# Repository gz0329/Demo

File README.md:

# Demo
Demotrates both programming and circuitry design projects.

circuit_pcb_design contains a collection of test circuits and PCBs that I designed with KiCAD.

script_work contains several script projects that have a variety of functions.
Detailed descriptions are in the code. Python oriented. 

EBI_moisture_sensor is a RF based moisture sensor that can detect water content in wood.
Firmware wise is C oriented. Circuits and PCBs are designed with KiCAD.
It also has several documentation samples such as BoM and Assembly instruction for board manufacturer.

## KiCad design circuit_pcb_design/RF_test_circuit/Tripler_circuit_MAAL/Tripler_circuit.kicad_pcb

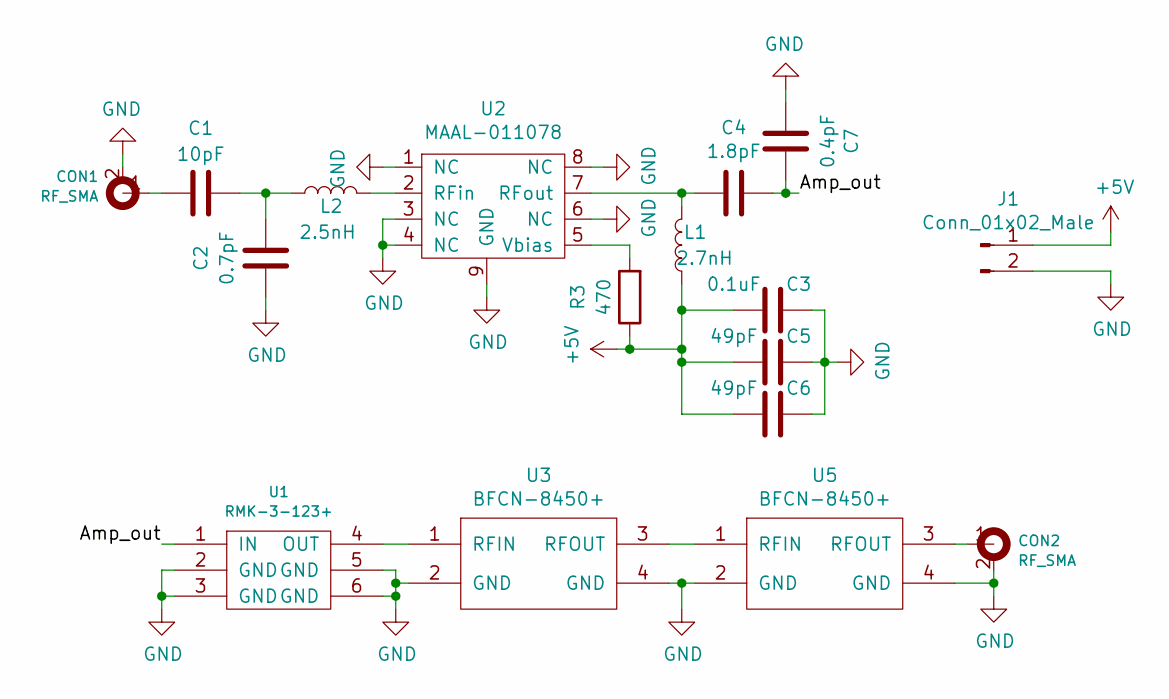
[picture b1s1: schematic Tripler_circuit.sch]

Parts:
C1: 10pF; C_0402
C2: 0.7pF; C_0402
C3: 0.1uF; C_0402
C4: 1.8pF; C_0402
C5, C6: 49pF; C_0603
C7: 0.4pF; C_0201_0603Metric
CON1, CON2: RF_SMA; SMAConnector
J1: Conn_01x02_Male; PinHeader_1x02_P2.54mm_Vertical
L1: 2.7nH; L_0402
L2: 2.5nH; L_0201_0603Metric
R3: 470; R_0603
U1: RMK-3-123+
U2: MAAL-011078
U3, U5: BFCN-8450+

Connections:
+5V: C3.2, C5.2, C6.2, J1.1, L1.1, R3.1
/Amp_out: C4.1, C7.1, U1.1 (IN)
GND: C2.1, C3.1, C5.1, C6.1, C7.2, CON1.2, CON2.2, J1.2, U1.2 (GND), U1.3 (GND), U1.5 (GND), U1.6 (GND), U2.1 (NC), U2.3 (NC), U2.4 (NC), U2.6 (NC), U2.8 (NC), U2.9 (GND), U3.2 (GND), U3.4 (GND), U5.2 (GND), U5.4 (GND)
unnamed: C1.1, CON1.1
unnamed: C1.2, C2.2, L2.1
unnamed: C4.2, L1.2, U2.7 (RFout)
unnamed: CON2.1, U5.3 (RFOUT)
unnamed: L2.2, U2.2 (RFin)
unnamed: R3.2, U2.5 (Vbias)
unnamed: U1.4 (OUT), U3.1 (RFIN)
unnamed: U3.3 (RFOUT), U5.1 (RFIN)

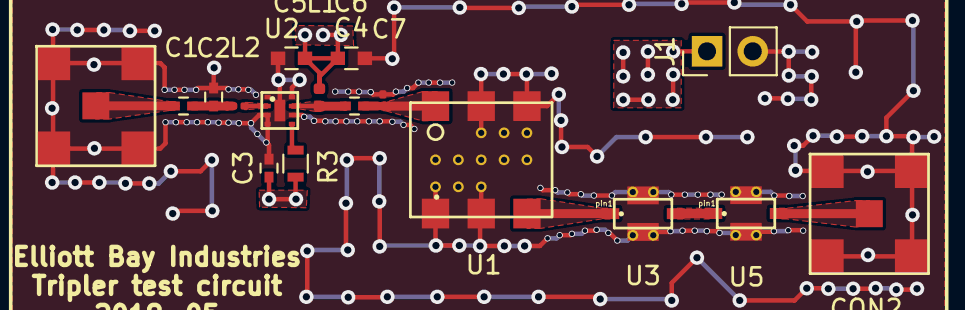
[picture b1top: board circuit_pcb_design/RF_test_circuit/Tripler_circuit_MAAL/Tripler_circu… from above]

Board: 4 copper layers, 17 parts (0 on the bottom side), 11 nets.

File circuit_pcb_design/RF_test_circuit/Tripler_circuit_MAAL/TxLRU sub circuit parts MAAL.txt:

TxLRU sub circuit parts MAAL

Amplifier
https://www.digikey.com/product-detail/en/MAAL-011078-TR1000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

2.5nH inductor 0201
https://www.digikey.com/product-detail/en/taiyo-yuden/HKQ060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

2.7nH inductor 0402
https://www.digikey.com/product-detail/en/taiyo-yuden/HK1005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

10pF cap 0402
https://www.digikey.com/product-detail/en/yageo/CC0402JRNPO9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

0.7pF cap 0402
https://www.digikey.com/product-detail/en/yageo/CC0402BRNPO9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

0.4pF cap 0201
https://www.digikey.com/product-detail/en/taiyo-yuden/UMK063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

1.8pF cap 0402
https://www.digikey.com/product-detail/en/yageo/CC0402CRNPO9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

0.1uF cap 0402
https://www.digikey.com/product-detail/en/taiyo-yuden/EMK105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

49pF cap 0603
https://www.digikey.com/product-detail/en/avx-corporation/06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

470ohm res 0603
https://www.digikey.com/product-detail/en/yageo/RC0603FR-074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

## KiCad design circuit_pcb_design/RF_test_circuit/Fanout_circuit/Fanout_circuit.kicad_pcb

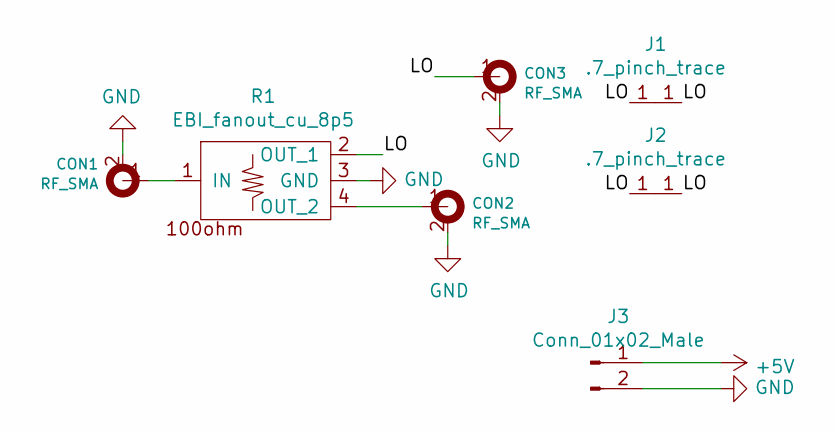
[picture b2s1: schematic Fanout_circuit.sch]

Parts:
CON1, CON2, CON3: RF_SMA; SMAConnector
J1, J2: .7_pinch_trace
J3: Conn_01x02_Male; PinHeader_1x02_P2.54mm_Vertical
R1: EBI_fanout_cu_8p5

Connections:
+5V: J3.1
/LO: CON3.1, J1.1, J2.1, R1.2 (OUT_1)
GND: CON1.2, CON2.2, CON3.2, J3.2, R1.3 (GND)
unnamed: CON1.1, R1.1 (IN)
unnamed: CON2.1, R1.4 (OUT_2)

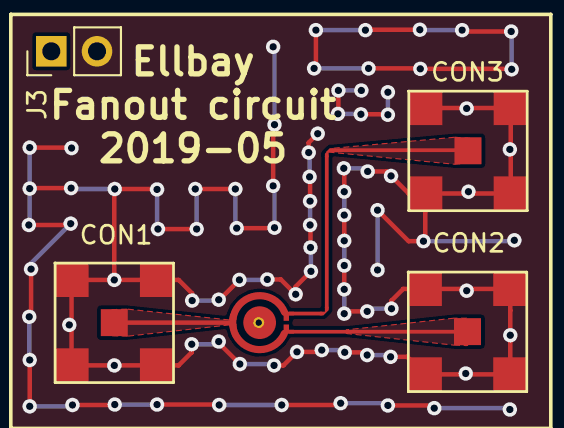
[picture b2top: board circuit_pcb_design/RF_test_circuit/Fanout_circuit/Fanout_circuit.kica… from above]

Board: 4 copper layers, 7 parts (0 on the bottom side), 4 nets.

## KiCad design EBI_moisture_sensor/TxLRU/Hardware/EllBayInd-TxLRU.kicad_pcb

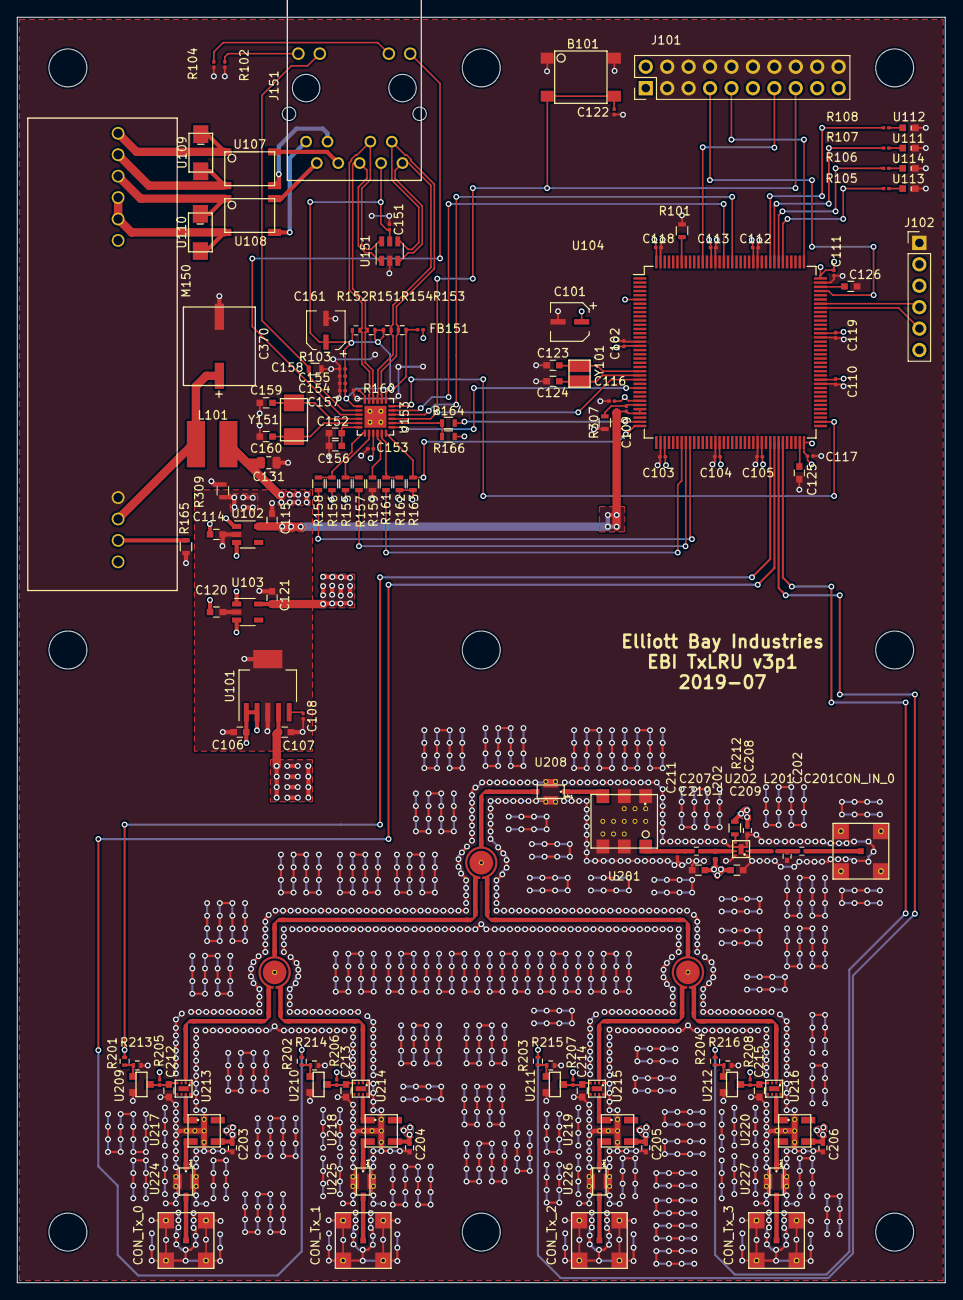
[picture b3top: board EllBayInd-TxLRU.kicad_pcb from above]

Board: 4 copper layers, 110.0 x 150.0 mm, 167 parts (0 on the bottom side), 96 nets.

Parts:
B101: Reset; Tactile_switch
C101, C161: 4.7uF; CP_Elec_4.3x4.3
C102, C103, C104, C105, C109, C110, C111, C112, C113, C116, C117, C118, C119, C122, C151, C153, C154, C155, C157, C158: 100nF; C_0201_0603Metric
C106, C125, C126: 2.2uF; C_0603
C107, C114, C115, C120, C121, C156: 1uF; C_0603
C108: 0.01uF; C_0201_0603Metric
C123, C124: 4.3pF; C_0603
C131: 10uF; C_0805_2012Metric
C152: 470pF; C_0603
C159, C160: 30pF; C_0603
C201: 10pF; C_0402
C202: 0.7pF; C_0402
C203, C204, C205, C206, C208: 0.1uF; C_0402
C207: 1.8pF; C_0402
C209, C210: 49pF; C_0603
C211: 0.4pF; C_0201_0603Metric
C212, C213, C214, C215: 0.01uF; C_0603
C370: 470uF; 470uF Cap
CON_IN_0: RF_SMA; SMAConnector
CON_Tx_0, CON_Tx_1, CON_Tx_2, CON_Tx_3: RF_SMA; SMAConnector
FB151: 600@100; L_0201_0603Metric
J101: SWD debugging; Program_Pin_Header
J102: Conn_01x06_UART1; PinHeader_1x06_P2.54mm_Vertical
J151: RJ45_7499211122A; RJ45
J201, J202, J203, J204, J205, J206, J207, J208, J209, J210, J211, J212, J213: .7_pinch_trace; .7_pinch_.537_trace
L101: 10uH; 10uH_Inductor
L201: 2.5nH; L_0201_0603Metric
L202: 2.7nH; L_0402
M150: AG9205S
MK201, MK202, MK203, MK204, MK205, MK206, MK207, MK208, MK209: Mounting_hole; MountingHole_4.5mm
R101, R103, R155, R156, R159, R162, R166: 10k; R_0603
R102, R104: 270; R_0201_0603Metric
R105, R106, R107, R108: 750; R_0201_0603Metric
R151, R152, R153, R154: 50; R_0402
R157, R158, R161, R164: 33; R_0603
R160: 12k1; R_0201_0603Metric
R163: 1k5; R_0603
R165: 0; R_0603
R201, R202, R203, R204: 100; R_0402
R205, R206, R207, R208: 4k; R_0201_0603Metric
R209, R210, R211: EBI_fanout_cu_8p5; EBI_fanout_cu_8p5_.537trace
R212: 470; R_0603
R213, R214, R215, R216: 10k; R_0402
R307, R309: Close; R_0603
U101: 5V_REG
U102, U103: 3V3_REG; 3V3REG
U104: STM32H743ZITx; MCU
U107, U108: MDB6S
U109, U110: SMAJ58CA
U111, U112, U113, U114: LED
U151: USBLC6-4SC6; TVS-diode
U153: LAN8742A
U201: RMK-3-123+
U202: MAAL-011078
U208, U224, U225, U226, U227: BFCN-8450+
U209, U210, U211, U212: NFET
U213, U214, U215, U216: MAAL-011130
U217, U218, U219, U220: TCBT-14+
Y101: 8 MHz; 8mhz_crystal
Y151: 25MHz; 25mhz_crystal

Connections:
+3.3VA: C109.1, C115.1, U102.5, U104.32, U104.33
+3V3: C101.1, C102.1, C103.1, C104.1, C105.1, C110.1, C111.1, C112.1, C113.1, C116.1, C117.1, C118.1, C119.1, C121.1, C153.2, FB151.2, J101.1, J101.2, R155.2, R156.2, R162.2, R163.2, R166.2, U103.5, U104.6, U104.17, U104.30, U104.39, U104.52, U104.62, U104.72, U104.84, U104.95, U104.108, U104.121, U104.131, U104.144, U153.9
+5V: C107.1, C203.1, C204.1, C205.1, C206.1, C208.2, C209.2, C210.2, L202.1, R205.2, R206.2, R207.2, R208.2, R212.2, U101.4, U217.3, U218.3, U219.3, U220.3
/Common/5.5V: C106.1, C114.1, C120.1, C131.2, L101.1, U101.1, U101.2, U102.1, U102.3, U103.1, U103.3
/Common/CRS_DV: R161.2, U104.43
/Common/LED0: R105.2, U104.114
/Common/LED1: R106.2, U104.115
/Common/LED2: R107.2, U104.116
/Common/LED3: R108.2, U104.117
/Common/MDC: U104.27, U153.13
/Common/MDIO: R163.1, U104.36, U153.12
/Common/NRST: B101.3, B101.4, C122.1, J101.15, U104.25, U153.15
/Common/RX_D0: R157.2, U104.44
/Common/RX_D1: R158.2, U104.45
/Common/SWCLK: J101.9, U104.109
/Common/SWDIO: J101.7, U104.105
/Common/Sheet5C53D1CF/LED_G: J151.13, R103.1, U153.2
/Common/Sheet5C53D1CF/LED_Y: J151.11, U153.3
/Common/Sheet5C53D1CF/RX+: J151.4, R152.2, U151.6, U153.23
/Common/Sheet5C53D1CF/RX-: J151.5, R151.2, U151.1, U153.22
/Common/Sheet5C53D1CF/TX+: J151.1, R154.2, U151.3, U153.21
/Common/Sheet5C53D1CF/TX-: J151.2, R153.2, U151.4, U153.20
/Common/Sheet5C53D1CF/VC1+: J151.7, U107.4
/Common/Sheet5C53D1CF/VC1-: J151.8, U107.3
/Common/Sheet5C53D1CF/VC2+: J151.9, U108.4
/Common/Sheet5C53D1CF/VC2-: J151.10, U108.3
/Common/TRACESWO: J101.13, U104.133
/Common/TX_D0: U104.128, U153.17
/Common/TX_D1: U104.74, U153.18
/Common/TX_EN: U104.126, U153.16
/Common/UART1_RX: J102.4, U104.102
/Common/UART1_TX: J102.5, U104.101
/Common/nINT: R164.2, U104.35
/LNA_out: C207.1, C211.1, U201.1
/LNA_out_0: U217.2, U224.1
/LNA_out_1: U218.2, U225.1
/LNA_out_2: U219.2, U226.1
/LNA_out_3: U220.2, U227.1
/LO: J201.1, J202.1, J203.1, J204.1, J205.1, J206.1, J207.1, J208.1, J209.1, J210.1, J211.1, J212.1, J213.1, R209.1, R209.2, R209.4, R210.1, R210.2, R210.4, R211.1, R211.2, R211.4, U208.3, U213.2, U214.2, U215.2, U216.2
/Switch_0: R201.2, U104.64
/Switch_1: R202.2, U104.65
/Switch_2: R203.2, U104.66
/Switch_3: R204.2, U104.67
/Tripler_out: U201.4, U208.1
GND: B101.1, B101.2, C101.2, C102.2, C103.2, C104.2, C105.2, C110.2, C111.2, C112.2, C113.2, C116.2, C117.2, C118.2, C119.2, C122.2, C123.2, C124.2, C125.2, C126.2, C131.1, C151.1, C152.1, C153.1, C154.1, C155.1, C156.1, C157.1, C158.1, C159.1, C160.1, C161.2, C202.1, C203.2, C204.2, C205.2, C206.2, C208.1, C209.1, C210.1, C211.2, C212.2, C213.2, C214.2, C215.2, C370.2, CON_IN_0.2, CON_Tx_0.2, CON_Tx_1.2, CON_Tx_2.2, CON_Tx_3.2, J101.3, J101.4, J101.5, J101.6, J101.8, J101.10, J101.12, J101.14, J101.16, J101.18, J101.20, J102.1, M150.7, R101.2, R102.2, R103.2, R104.2, R159.2, R160.1, R165.1, R209.3, R210.3, R211.3, R213.2, R214.2, R215.2, R216.2, R307.2, R309.1, U104.16, U104.38, U104.51, U104.61, U104.83, U104.94, U104.107, U104.120, U104.130, U104.143, U111.1, U112.1, U113.1, U114.1, U151.2, U153.25, U201.2, U201.3, U201.5, U201.6, U202.1, U202.3, U202.4, U202.6, U202.8, U202.9, U208.2, U208.4, U209.3, U210.3, U211.3, U212.3, U213.1, U213.8, U214.1, U214.8, U215.1, U215.8, U216.1, U216.8, U217.5, U218.5, U219.5, U220.5, U224.2, U224.4, U225.2, U225.4, U226.2, U226.4, U227.2, U227.4
GNDA: C109.2, R307.1, U104.31
GNDPWR: C106.2, C107.2, C108.2, C114.2, C115.2, C120.2, C121.2, R309.2, U101.3, U101.6, U102.2, U103.2
unnamed: C108.1, U101.5
unnamed: C123.1, U104.23, Y101.1
unnamed: C124.1, U104.24, Y101.2
unnamed: C125.1, U104.71
unnamed: C126.1, U104.106
unnamed: C151.2, C154.2, C155.2, C157.2, C158.2, C161.1, FB151.1, J151.3, R151.1, R152.1, R153.1, R154.1, U151.5, U153.1, U153.19
unnamed: C152.2, C156.2, U153.6
unnamed: C159.2, U153.4, Y151.2
unnamed: C160.2, U153.5, Y151.1
unnamed: C201.1, C202.2, L201.2
unnamed: C201.2, CON_IN_0.1
unnamed: C207.2, L202.2, U202.7
unnamed: C212.1, R205.1, U209.1, U213.4
unnamed: C213.1, R206.1, U210.1, U214.4
unnamed: C214.1, R207.1, U211.1, U215.4
unnamed: C215.1, R208.1, U212.1, U216.4
unnamed: C370.1, L101.2, M150.8
unnamed: CON_Tx_0.1, U224.3
unnamed: CON_Tx_1.1, U225.3
unnamed: CON_Tx_2.1, U226.3
unnamed: CON_Tx_3.1, U227.3
unnamed: J151.12, R104.1
unnamed: J151.14, R102.1
unnamed: L201.1, U202.2
unnamed: M150.1, U107.1, U109.1
unnamed: M150.2, U107.2, U109.2
unnamed: M150.3, U108.1, U110.1
unnamed: M150.4, M150.5, U108.2, U110.2
unnamed: M150.9, R165.2
unnamed: R101.1, U104.138
unnamed: R105.1, U113.2
unnamed: R106.1, U114.2
unnamed: R107.1, U111.2
unnamed: R108.1, U112.2
unnamed: R155.1, R157.1, U153.8
unnamed: R156.1, R158.1, U153.7
unnamed: R159.1, U153.10
unnamed: R160.2, U153.24
unnamed: R161.1, R162.1, U153.11
unnamed: R164.1, R166.1, U153.14
unnamed: R201.1, R213.1, U209.2
unnamed: R202.1, R214.1, U210.2
unnamed: R203.1, R215.1, U211.2
unnamed: R204.1, R216.1, U212.2
unnamed: R212.1, U202.5
unnamed: U213.7, U217.1
unnamed: U214.7, U218.1
unnamed: U215.7, U219.1
unnamed: U216.7, U220.1

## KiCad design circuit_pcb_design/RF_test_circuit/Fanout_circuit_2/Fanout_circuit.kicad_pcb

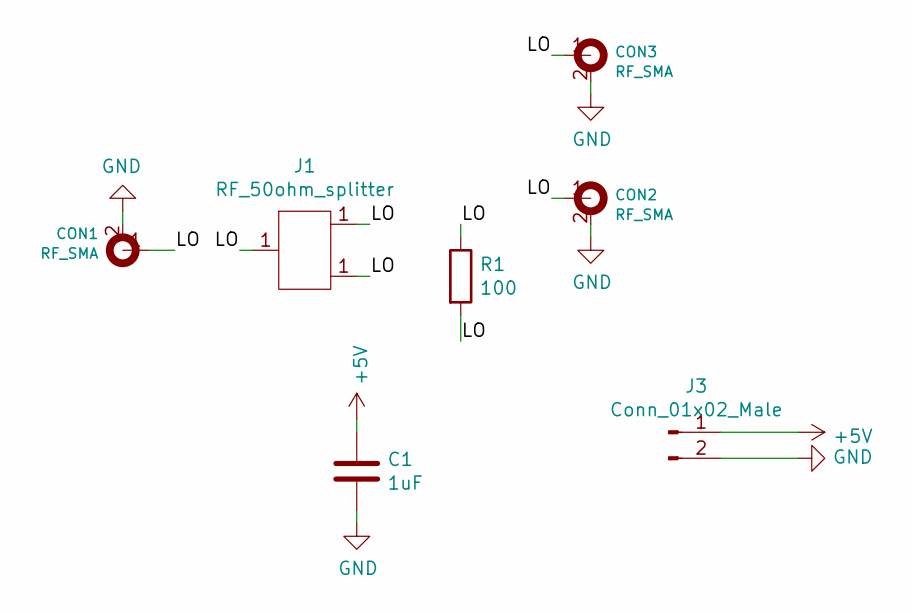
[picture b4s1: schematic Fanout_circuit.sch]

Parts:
C1: 1uF; C_0402
CON1, CON2, CON3: RF_SMA; SMAConnector
J1: RF_50ohm_splitter; RF_50ohm_splitter_effective
J3: Conn_01x02_Male; PinHeader_1x02_P2.54mm_Vertical
R1: 100; R_0402

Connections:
+5V: C1.1, J3.1
/LO: CON1.1, CON2.1, CON3.1, J1.1, R1.1, R1.2
GND: C1.2, CON1.2, CON2.2, CON3.2, J3.2

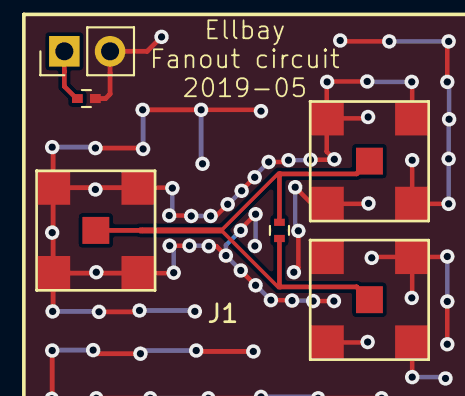
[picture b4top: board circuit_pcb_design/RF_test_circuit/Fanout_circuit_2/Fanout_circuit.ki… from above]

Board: 4 copper layers, 7 parts (0 on the bottom side), 3 nets.

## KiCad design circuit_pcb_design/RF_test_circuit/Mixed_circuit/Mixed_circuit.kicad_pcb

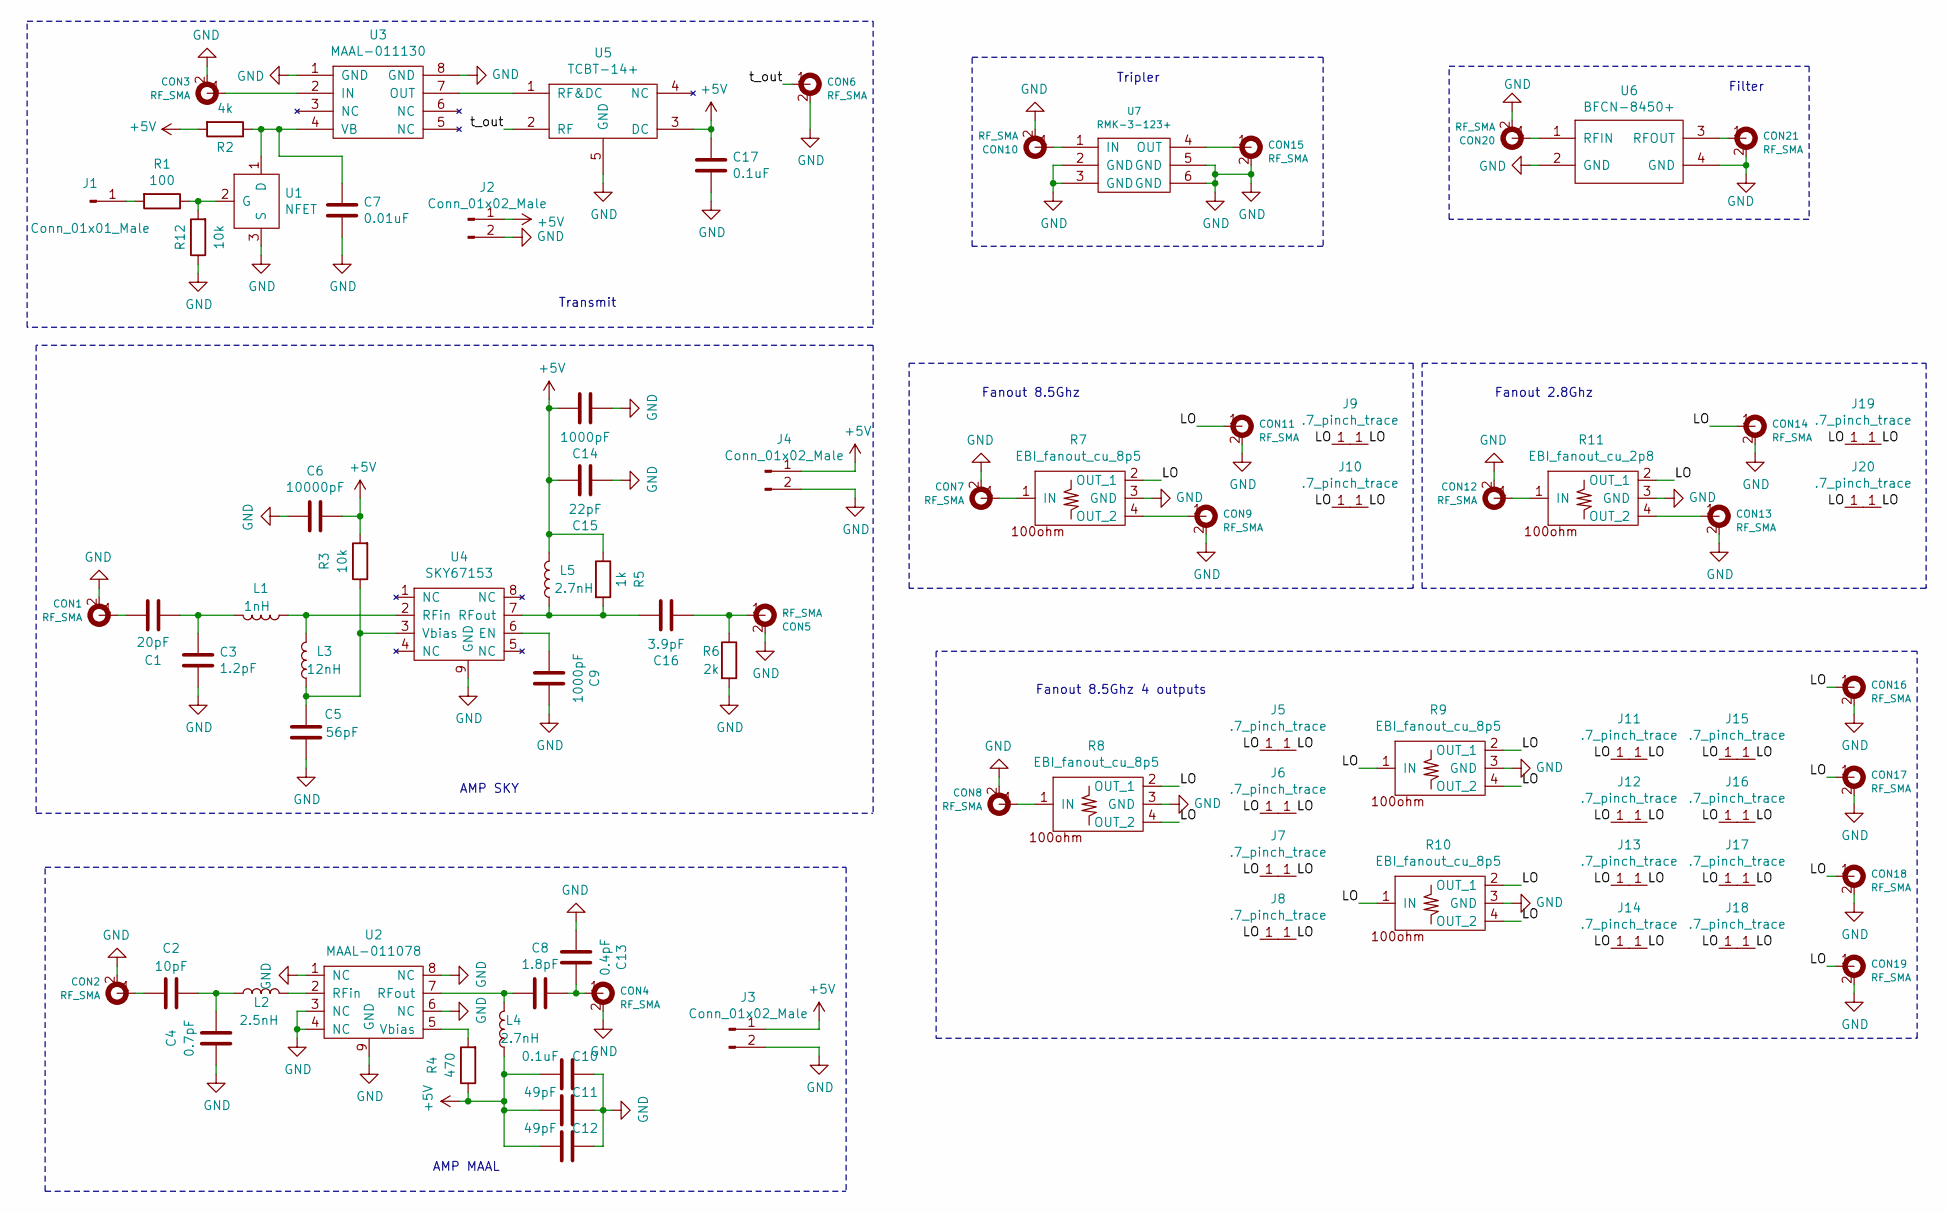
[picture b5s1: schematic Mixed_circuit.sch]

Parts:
C1: 20pF; C_0402
C2: 10pF; C_0402
C3: 1.2pF; C_0402
C4: 0.7pF; C_0402
C5: 56pF; C_0402
C6: 10000pF; C_0402
C7: 0.01uF; C_0603
C8: 1.8pF; C_0402
C9, C14: 1000pF; C_0402
C10, C17: 0.1uF; C_0402
C11, C12: 49pF; C_0603
C13: 0.4pF; C_0201_0603Metric
C15: 22pF; C_0402
C16: 3.9pF; C_0402
CON1, CON2, CON3, CON4, CON5, CON6, CON7, CON8, CON9, CON10, CON11, CON12, CON13, CON14, CON15, CON16, CON17, CON18, CON19, CON20, CON21: RF_SMA; SMA_Edge
J1: Conn_01x01_Male; PinHeader_1x01_P2.54mm_Vertical
J2, J3, J4: Conn_01x02_Male; PinHeader_1x02_P2.54mm_Vertical
J5, J6, J7, J8, J9, J10, J11, J12, J13, J14, J15, J16, J17, J18, J19, J20: .7_pinch_trace; .7_pinch_.537_trace
L1: 1nH; L_0402
L2: 2.5nH; L_0201_0603Metric
L3: 12nH; L_0402
L4, L5: 2.7nH; L_0402
R1: 100; R_0402
R2: 4k; R_0201_0603Metric
R3, R12: 10k; R_0402
R4: 470; R_0603
R5: 1k; R_0402
R6: 2k; R_0402
R7, R8, R9, R10: EBI_fanout_cu_8p5; EBI_fanout_cu_8p5_.537trace
R11: EBI_fanout_cu_2p8; EBI_fanout_cu_2p8_.537trace
U1: NFET
U2: MAAL-011078
U3: MAAL-011130
U4: SKY67153
U5: TCBT-14+
U6: BFCN-8450+
U7: RMK-3-123+

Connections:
+5V: C6.1, C10.2, C11.2, C12.2, C14.1, C15.1, C17.1, J2.1, J3.1, J4.1, L4.1, L5.2, R2.2, R3.2, R4.1, R5.1, U5.3 (DC)
/LO: CON11.1, CON14.1, CON16.1, CON17.1, CON18.1, CON19.1, J5.1, J6.1, J7.1, J8.1, J9.1, J10.1, J11.1, J12.1, J13.1, J14.1, J15.1, J16.1, J17.1, J18.1, J19.1, J20.1, R7.2 (OUT_1), R8.2 (OUT_1), R8.4 (OUT_2), R9.1 (IN), R9.2 (OUT_1), R9.4 (OUT_2), R10.1 (IN), R10.2 (OUT_1), R10.4 (OUT_2), R11.2 (OUT_1)
/t_out: CON6.1, U5.2 (RF)
GND: C3.1, C4.1, C5.1, C6.2, C7.2, C9.1, C10.1, C11.1, C12.1, C13.2, C14.2, C15.2, C17.2, CON1.2, CON2.2, CON3.2, CON4.2, CON5.2, CON6.2, CON7.2, CON8.2, CON9.2, CON10.2, CON11.2, CON12.2, CON13.2, CON14.2, CON15.2, CON16.2, CON17.2, CON18.2, CON19.2, CON20.2, CON21.2, J2.2, J3.2, J4.2, R6.2, R7.3 (GND), R8.3 (GND), R9.3 (GND), R10.3 (GND), R11.3 (GND), R12.1, U1.3 (S), U2.1 (NC), U2.3 (NC), U2.4 (NC), U2.6 (NC), U2.8 (NC), U2.9 (GND), U3.1 (GND), U3.8 (GND), U4.9 (GND), U5.5 (GND), U6.2 (GND), U6.4 (GND), U7.2 (GND), U7.3 (GND), U7.5 (GND), U7.6 (GND)
unnamed: C1.1, C3.2, L1.2
unnamed: C1.2, CON1.1
unnamed: C2.1, CON2.1
unnamed: C2.2, C4.2, L2.1
unnamed: C5.2, L3.1, R3.1, U4.3 (Vbias)
unnamed: C7.1, R2.1, U1.1 (D), U3.4 (VB)
unnamed: C8.2, L4.2, U2.7 (RFout)
unnamed: C9.2, U4.6 (EN)
unnamed: C8.1, C13.1, CON4.1
unnamed: C16.1, L5.1, R5.2, U4.7 (RFout)
unnamed: C16.2, CON5.1, R6.1
unnamed: CON3.1, U3.2 (IN)
unnamed: CON7.1, R7.1 (IN)
unnamed: CON8.1, R8.1 (IN)
unnamed: CON9.1, R7.4 (OUT_2)
unnamed: CON10.1, U7.1 (IN)
unnamed: CON12.1, R11.1 (IN)
unnamed: CON13.1, R11.4 (OUT_2)
unnamed: CON15.1, U7.4 (OUT)
unnamed: CON20.1, U6.1 (RFIN)
unnamed: CON21.1, U6.3 (RFOUT)
unnamed: J1.1, R1.2
unnamed: L1.1, L3.2, U4.2 (RFin)
unnamed: L2.2, U2.2 (RFin)
unnamed: R1.1, R12.2, U1.2 (G)
unnamed: R4.2, U2.5 (Vbias)
unnamed: U3.7 (OUT), U5.1 (RF&DC)

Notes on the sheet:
AMP MAAL
AMP SKY
Transmit
Fanout 8.5Ghz
Fanout 2.8Ghz
Fanout 8.5Ghz 4 outputs
Tripler
Filter

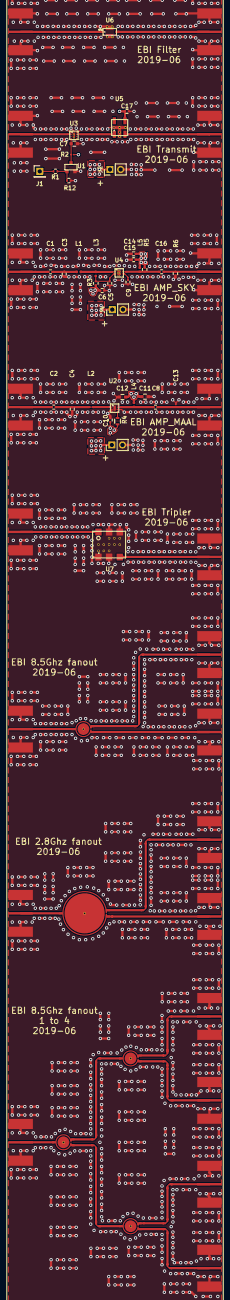
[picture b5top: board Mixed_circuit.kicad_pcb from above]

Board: 4 copper layers, 82 parts (0 on the bottom side), 31 nets.

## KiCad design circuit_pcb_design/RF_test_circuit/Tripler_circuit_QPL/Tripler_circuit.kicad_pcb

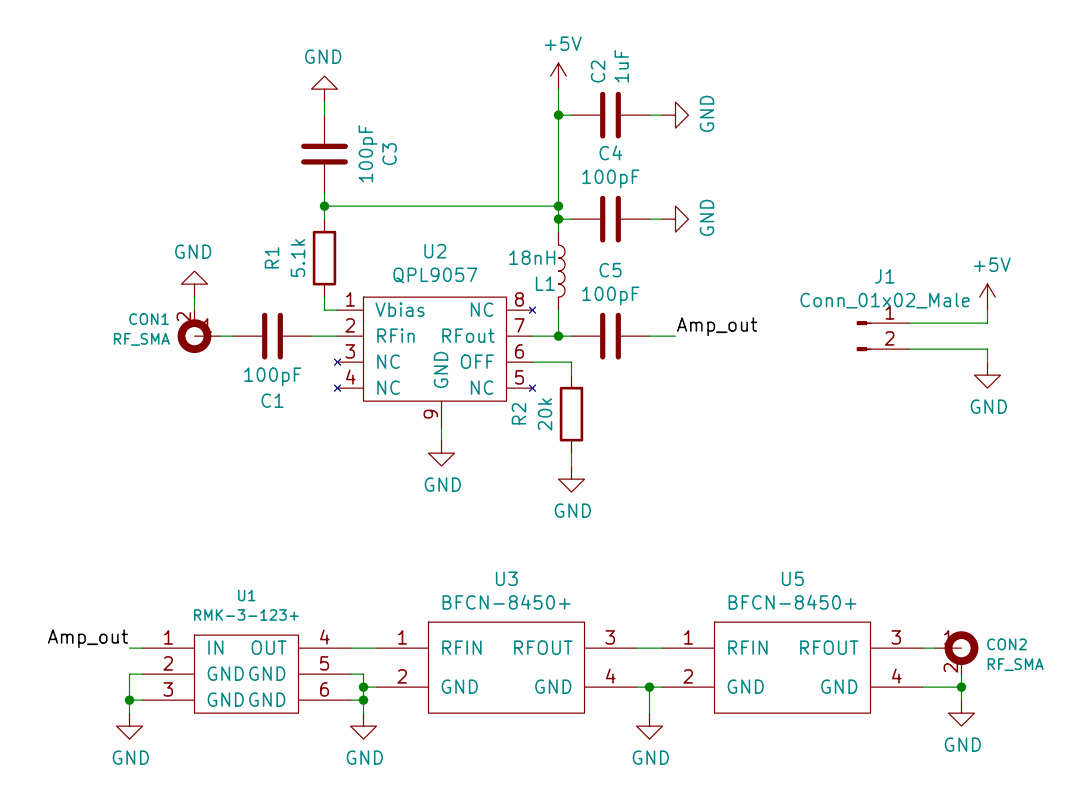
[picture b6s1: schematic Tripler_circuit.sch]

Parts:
C1, C3, C4, C5: 100pF; C_0201_0603Metric
C2: 1uF; C_0603
CON1, CON2: RF_SMA; SMAConnector
J1: Conn_01x02_Male; PinHeader_1x02_P2.54mm_Vertical
L1: 18nH; L_0402
R1: 5.1k; R_0603
R2: 20k; R_0402
U1: RMK-3-123+
U2: QPL9057
U3, U5: BFCN-8450+

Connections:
+5V: C2.2, C3.1, C4.2, J1.1, L1.1, R1.2
/Amp_out: C5.1, U1.1 (IN)
GND: C2.1, C3.2, C4.1, CON1.2, CON2.2, J1.2, R2.1, U1.2 (GND), U1.3 (GND), U1.5 (GND), U1.6 (GND), U2.9 (GND), U3.2 (GND), U3.4 (GND), U5.2 (GND), U5.4 (GND)
unnamed: C1.1, U2.2 (RFin)
unnamed: C1.2, CON1.1
unnamed: C5.2, L1.2, U2.7 (RFout)
unnamed: CON2.1, U5.3 (RFOUT)
unnamed: R1.1, U2.1 (Vbias)
unnamed: R2.2, U2.6 (OFF)
unnamed: U1.4 (OUT), U3.1 (RFIN)
unnamed: U3.3 (RFOUT), U5.1 (RFIN)

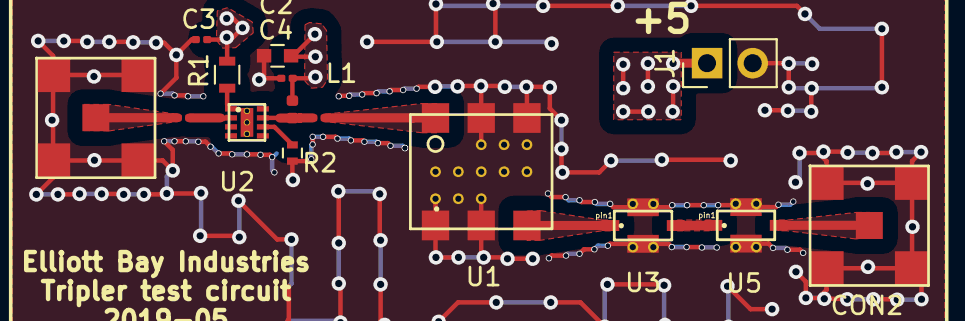
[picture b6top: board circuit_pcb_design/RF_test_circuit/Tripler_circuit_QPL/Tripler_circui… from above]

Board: 4 copper layers, 15 parts (0 on the bottom side), 11 nets.
